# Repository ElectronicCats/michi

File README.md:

# Michi

</p>

  Michi is an electronic board designed by Electronic Cats that simulates configurable keyboard and mouse keys. It has the feature of being able to connect to any conductive material, turning these objects into touch panels. 

  It is an experiment kit for beginners and experts looking to interact between the real world and technology. The Michi can cover the areas of plastic arts, visual arts, music, sports, engineering and even physical rehabilitation.

## For whom is Michi? 

  People 6 years and older, educators, artists, engineers, designers, inventors and creators. 

## How does it work?

  The Michi uses high resistance switching to detect when it has made a connection even with materials that are not very conductive (such as leaves, pasta or people). This technique attracts, Michi can also act as a keyboard or mouse. There are 10 inputs on the front of the board, which can be linked via alligator wires or any other method you can think of. There are another 5 inputs on the back, 3 for keyboard keys and 2 for mouse movement, which can be accessed with jumpers.

  For example, when you connect and touch an apple, you make a connection, and Michi sends the computer a keyboard message. The computer sees Michi as an ordinary keyboard (or mouse). Therefore, it works with all programs, operating systems and web pages, since all programs and web pages receive information from the keyboard and mouse.

## What materials work with Michi?

  Any material that can conduct a little electricity will work. Here are some materials that people have used in our workshops: Ketchup or tomato sauce, Pencil Graphite, Finger Paint, Lemons, etc.

  Other materials that work very well: plants, coins, silverware, anything wet, most foods, aluminum foil, water, and hundreds of things we haven't tried.

## What can I do?

  That's up to you! First, load a computer program or any web page. Let's say you load a piano. Then, instead of using the buttons on the computer keyboard to play the piano, you can connect Michi to something fun, like bananas, and the bananas become your piano keys. 

  Or let's say you search for a Pacman game online and draw a joystick with a pencil. Then you can play Pacman by touching the drawing. 
  The kit includes everything you need: Michi Board, alligator cable, USB cable.

## Manual

Visit our Wiki where you can find the manual 📖: [Wiki](https://github.com/ElectronicCats/michi/wiki)

## How to contribute 
 Contributions are welcome! 

Please read the document  [**Contribution Manual**](https://github.com/ElectronicCats/electroniccats-cla/blob/main/electroniccats-contribution-manual.md)  which will show you how to contribute your changes to the project.

✨ Thanks to all our [contributors](https://github.com/ElectronicCats/michi/graphs/contributors)! ✨

See  [**_Electronic Cats CLA_**](https://github.com/ElectronicCats/electroniccats-cla/blob/main/electroniccats-cla.md) for more information.

See the [**community code of conduct**](https://github.com/ElectronicCats/electroniccats-cla/blob/main/electroniccats-community-code-of-conduct.md)   for a vision of the community we want to build and what we expect from it.

### Maintainer

Electronic Cats invests time and resources in providing this open-source design design, please support Electronic Cats and open-source hardware by purchasing products from Electronic Cats!

## Licence

Firmware released under an GNU AGPL v3.0 license. See the [LICENSE](https://www.gnu.org/licenses/agpl-3.0.en.html) file for more information.

Hardware released under an CERN Open Hardware Licence v1.2. See the [LICENSE_HARDWARE](https://ohwr.org/project/licences/wikis/cern-ohl-v1.2) file for more information.

Electronic Cats is a registered trademark, please do not use if you sell these PCBs.

Electronic Cats invests time and resources providing this open source design, please support Electronic Cats and open-source hardware by purchasing products from Electronic Cats!

Designed by Electronic Cats.

30 Jul 2022

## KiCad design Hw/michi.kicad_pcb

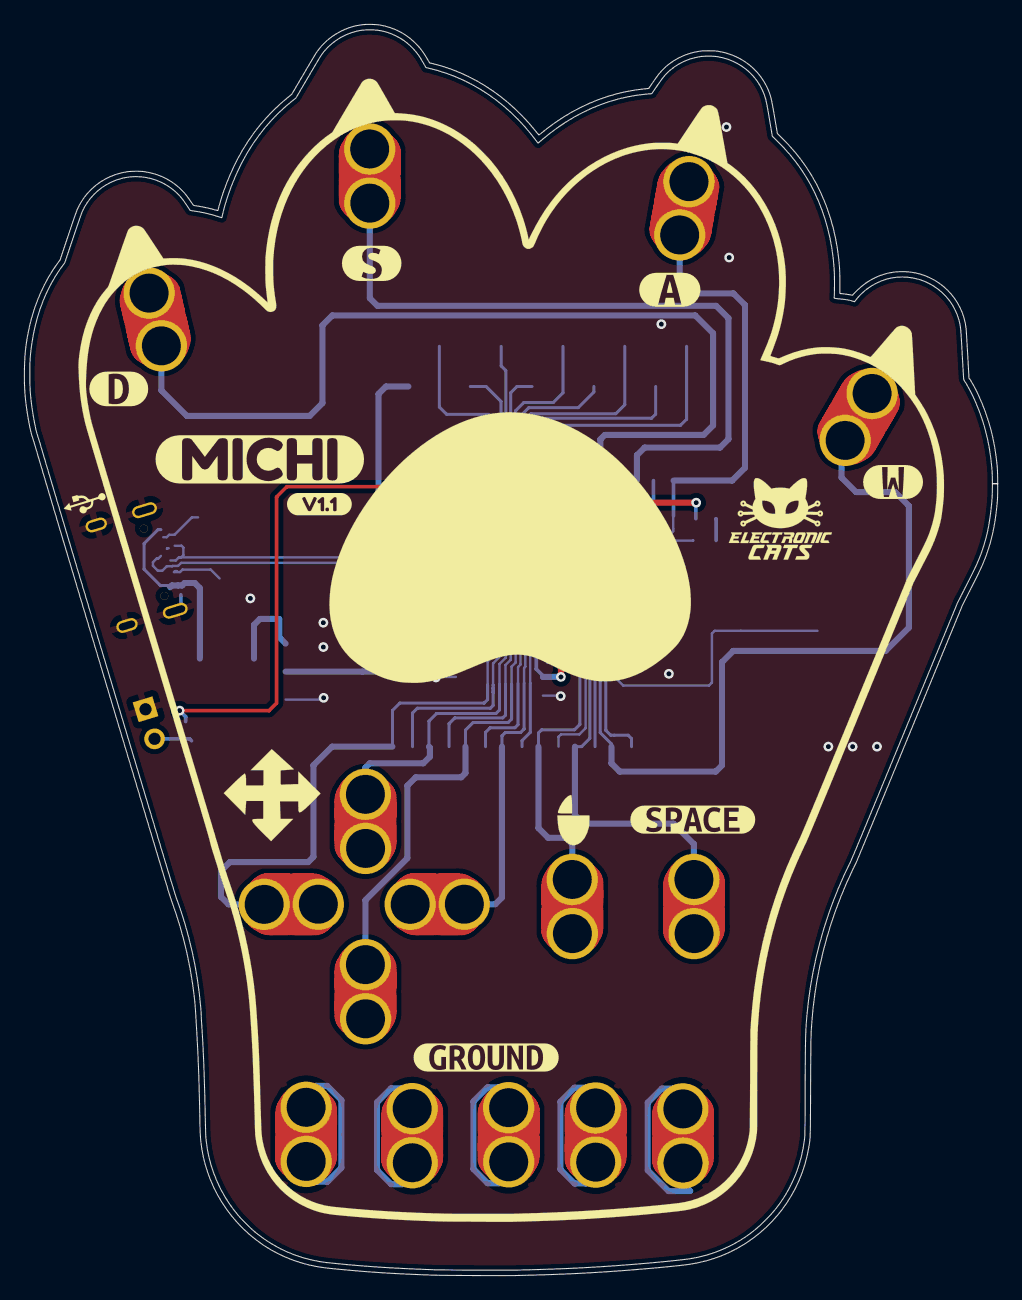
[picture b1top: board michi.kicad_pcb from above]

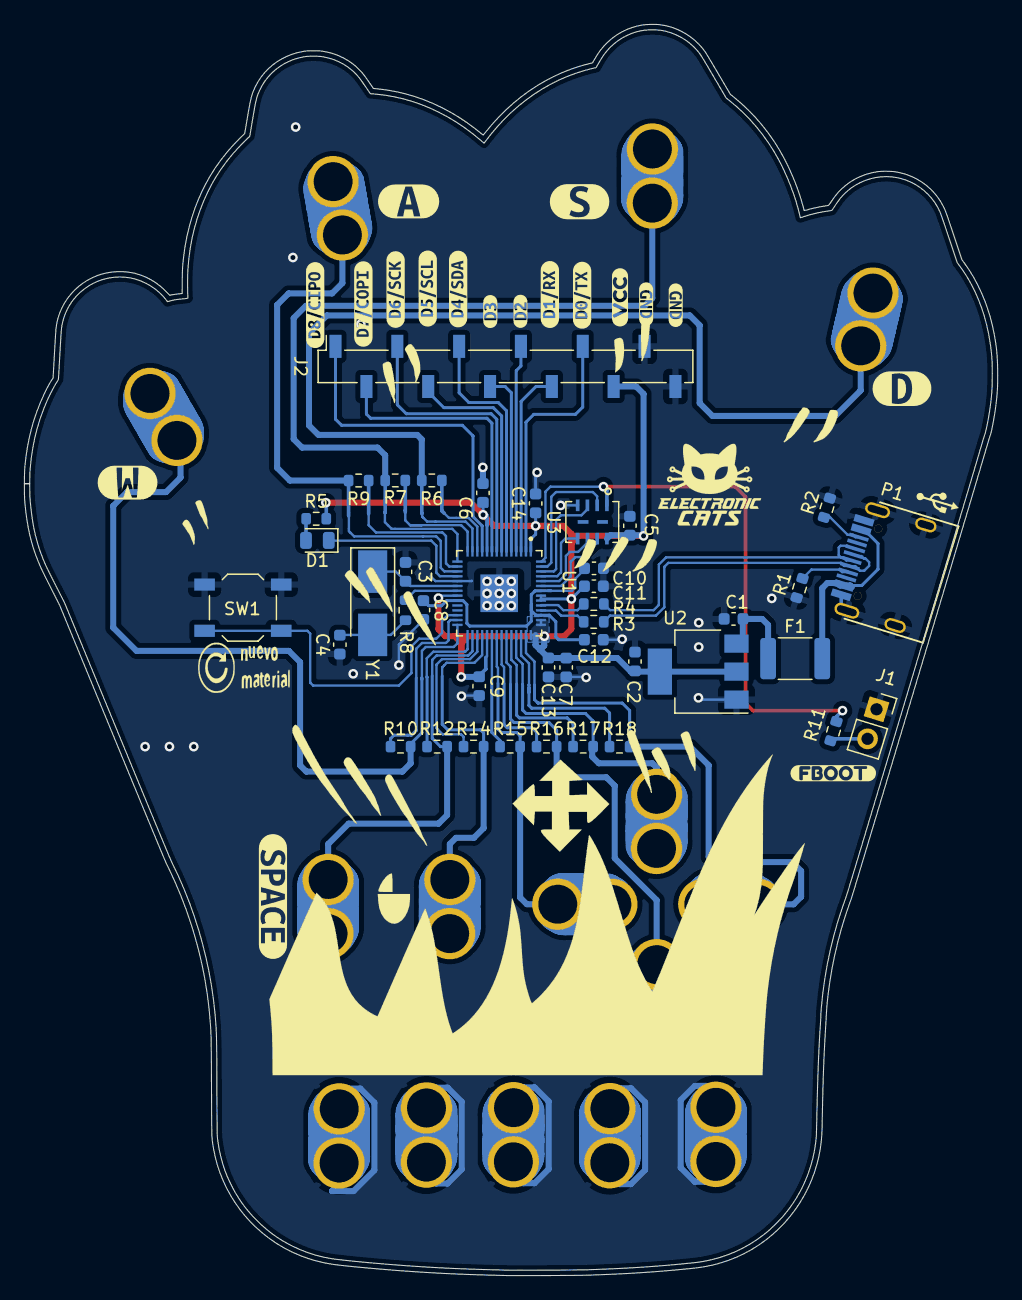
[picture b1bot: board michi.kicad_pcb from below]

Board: 2 copper layers, 80.0 x 102.8 mm, 85 parts (61 on the bottom side), 53 nets.

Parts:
C1, C2: 10uf; C_0603_1608Metric
C3, C4: 27pf; C_0603_1608Metric
C5, C7, C9, C10, C11, C12, C13, C14: .1uf; C_0603_1608Metric
C6, C8: 1uf; C_0603_1608Metric
D1: LED; D_0805_2012Metric
F1: 0.5A; Fuse_1812_4532Metric_Pad1.30x3.40mm_HandSolder
J1: Conn_01x02; PinSocket_1x02_P2.54mm_Vertical
J2: Conn_Right; PinSocket_1x12_P2.54mm_Vertical_SMD_Pin1Right
P1: USB_C_Plug_USB2.0; C393939
P6, P6#2, P6#3, P6#4, P6#5, P6#6, P6#7, P6#8, P6#9, P6#10, P6#11, P6#12, P6#13, P6#14, P6#15: D; SEWALLI_renew
R1, R2: 5.1K; R_0603_1608Metric
R3, R4: 27.4; R_0603_1608Metric
R5, R8, R11: 1k; R_0603_1608Metric
R6, R7, R9, R10, R12, R14, R15, R16, R17, R18: 22M; R_0603_1608Metric
Ref**: Val**; PCB_Michi_Act
SW1: SW_Push; SW_SPST_TL3342
U1: RP2040; QFN40P700X700X90-57N
U2: NCP1117ST33T3G; SOT-223-3_TabPin2
U3: W25Q128JVS; W25Q16JVUUIQ
Y1: Crystal; Crystal_SMD_5032-2Pin_5.0x3.2mm_HandSoldering
kibuzzard-63055E6D, kibuzzard-63055E6D#2: G***; kibuzzard-63055E6D
kibuzzard-63055E8E, kibuzzard-63055E8E#2: G***; kibuzzard-63055E8E
kibuzzard-63055E62, kibuzzard-63055E62#2: G***; kibuzzard-63055E62
kibuzzard-63055EA5, kibuzzard-63055EA5#2: G***; kibuzzard-63055EA5
kibuzzard-63055F28: G***; kibuzzard-63055F28
kibuzzard-63055FE6, kibuzzard-63055FE6#2: G***; kibuzzard-63055FE6
kibuzzard-630561F0: G***; kibuzzard-630561F0
kibuzzard-630562A3, kibuzzard-630562A3#2: G***; kibuzzard-630562A3
kibuzzard-630562BF: G***; kibuzzard-630562BF
kibuzzard-639765AD: G***; kibuzzard-639765AD
kibuzzard-639765C9: G***; kibuzzard-639765C9
kibuzzard-6305622D: G***; kibuzzard-6305622D
kibuzzard-6305624B: G***; kibuzzard-6305624B
kibuzzard-6305640E: G***; kibuzzard-6305640E
kibuzzard-6449595B: G***; kibuzzard-6449595B
kibuzzard-63056210: G***; kibuzzard-63056210
kibuzzard-63056260: G***; kibuzzard-63056260
kibuzzard-63056270: G***; kibuzzard-63056270
kibuzzard-63056280: G***; kibuzzard-63056280
kibuzzard-63056299: G***; kibuzzard-63056299
svg2mod, svg2mod#2: G***; usb_graphic

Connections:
+1V1: C8.1, C10.1, C12.1, U1.23 (DVDD), U1.45 (VREG_VOUT), U1.50 (DVDD)
+3V3: C2.1, C5.1, C6.1, C7.1, C9.1, C11.1, C13.1, C14.1, J2.10, R5.2, U1.1 (IOVDD), U1.10 (IOVDD), U1.22 (IOVDD), U1.33 (IOVDD), U1.42 (IOVDD), U1.43 (ADC_AVDD), U1.44 (VREG_VIN), U1.48 (USB_VDD), U1.49 (IOVDD), U2.2 (VO), U3.8 (VCC)
/D+: P1.A6 (D+), R4.2
/D-: P1.A7 (D-), R3.2
/DR+: R4.1, U1.47 (USB_DP)
/DR-: R3.1, U1.46 (USB_DM)
/IO0: J2.9, U1.2 (GPIO0)
/IO1: J2.8, U1.3 (GPIO1)
/IO2: J2.7, U1.4 (GPIO2)
/IO3: J2.6, U1.5 (GPIO3)
/IO4: J2.5, U1.6 (GPIO4)
/IO5: J2.4, U1.7 (GPIO5)
/IO6: J2.3, U1.8 (GPIO6)
/IO7: J2.2, U1.9 (GPIO7)
/IO8: J2.1, U1.11 (GPIO8)
/IO9: R6.2, U1.12 (GPIO9)
/IO10: P6#10.1, R6.1, U1.13 (GPIO10)
/IO11: R7.2, U1.14 (GPIO11)
/IO12: P6#12.1, R7.1, U1.15 (GPIO12)
/IO13: R9.2, U1.16 (GPIO13)
/IO14: P6.1, R9.1, U1.17 (GPIO14)
/IO15: D1.1 (K), U1.18 (GPIO15)
/IO16: R10.2, U1.27 (GPIO16)
/IO17: P6#11.1, R10.1, U1.28 (GPIO17)
/IO18: R12.2, U1.29 (GPIO18)
/IO19: P6#15.1, R12.1, U1.30 (GPIO19)
/IO20: R14.2, U1.31 (GPIO20)
/IO21: P6#8.1, R14.1, U1.32 (GPIO21)
/IO22: R15.2, U1.34 (GPIO22)
/IO23: P6#6.1, R15.1, U1.35 (GPIO23)
/IO24: R16.2, U1.36 (GPIO24)
/IO25: P6#2.1, R16.1, U1.37 (GPIO25)
/IO26: R17.2, U1.38 (GPIO26/ADC0)
/IO27: P6#3.1, R17.1, U1.39 (GPIO27/ADC1)
/IO28: R18.2, U1.40 (GPIO28/ADC2)
/IO29: P6#7.1, R18.1, U1.41 (GPIO29/ADC3)
/RST: SW1.1, U1.26 (RUN)
/SCLK: U1.52 (QSPI_SCLK), U3.6 (CLK)
/SD1: U1.55 (QSPI_SD1), U3.2 (DO(IO1))
/SD2: U1.54 (QSPI_SD2), U3.3 (IO2)
/SD3: U1.51 (QSPI_SD3), U3.7 (IO3)
/SDO: U1.53 (QSPI_SD0), U3.5 (DI(IO0))
/SS: R11.2, U1.56 (QSPI_CSN), U3.1 (~CS)
/XIN: C3.2, U1.20 (XIN), Y1.1
/XOUT: R8.1, U1.21 (XOUT)
GND: C1.2, C2.2, C3.1, C4.1, C5.2, C6.2, C7.2, C8.2, C9.2, C10.2, C11.2, C12.2, C13.2, C14.2, J1.1, J2.11, J2.12, P1.A1 (GND), P1.S1 (SHIELD), P6#4.1, P6#5.1, P6#9.1, P6#13.1, P6#14.1, R1.2, R2.2, SW1.2, U1.19 (TESTEN), U1.57 (GND), U2.1 (GND), U3.4 (GND)
unnamed: C4.2, R8.2, Y1.2
unnamed: D1.2 (A), R5.1
unnamed: F1.2, P1.A4 (VBUS)
unnamed: J1.2, R11.1
unnamed: P1.A5 (CC), R1.1
unnamed: P1.B5 (VCONN), R2.1
VBUS: C1.1, F1.1, U2.3 (VI)

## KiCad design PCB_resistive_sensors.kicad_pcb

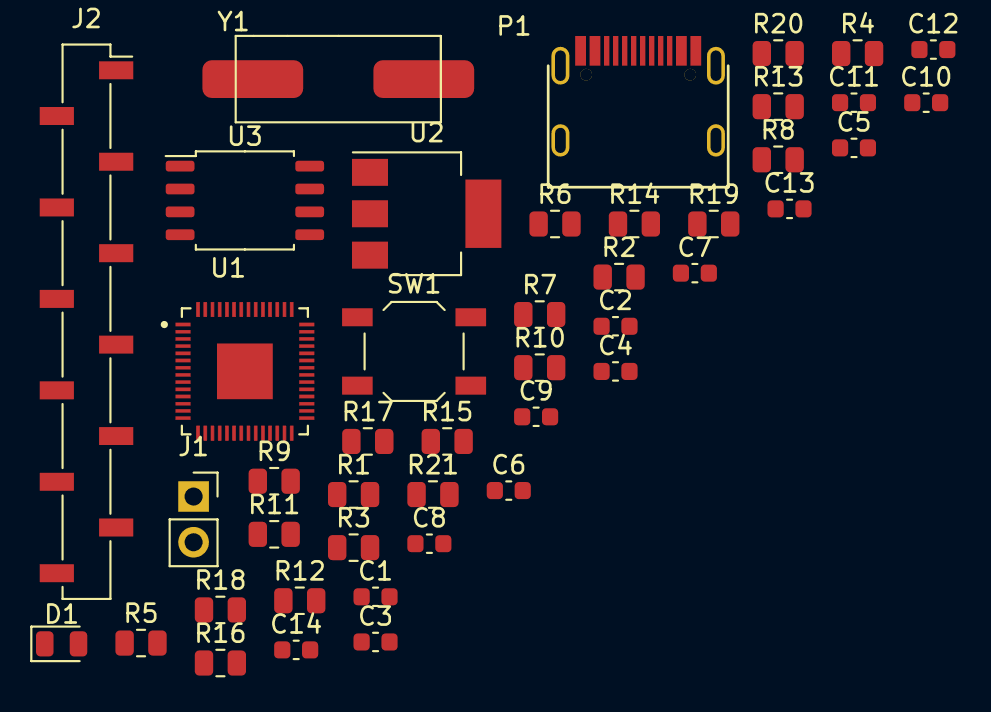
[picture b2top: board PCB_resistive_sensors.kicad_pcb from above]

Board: 2 copper layers, 44 parts (0 on the bottom side), 51 nets, no tracks yet.

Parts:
C1, C2: 10uf; C_0603_1608Metric
C3, C4: 27pf; C_0603_1608Metric
C5, C7, C9, C10, C11, C12, C13, C14: .1uf; C_0603_1608Metric
C6, C8: 1uf; C_0603_1608Metric
D1: LED; D_0805_2012Metric
J1: Conn_01x02; PinSocket_1x02_P2.54mm_Vertical
J2: Conn_Right; PinSocket_1x12_P2.54mm_Vertical_SMD_Pin1Right
P1: USB_C_Plug_USB2.0; C393939
R1, R2: 5.1K; R_0805_2012Metric
R3, R4: 27.4; R_0805_2012Metric
R5, R8, R11: 1k; R_0805_2012Metric
R6, R7, R9, R10, R12, R14, R15, R16, R17, R18, R19, R20: 22M; R_0805_2012Metric
R13: DNF; R_0805_2012Metric
R21: 10k; R_0805_2012Metric
SW1: SW_Push; SW_SPST_TL3342
U1: RP2040; QFN40P700X700X90-57N
U2: NCP1117ST33T3G; SOT-223-3_TabPin2
U3: W25Q128JVS; SOIC-8_5.23x5.23mm_P1.27mm
Y1: Crystal; ABLS-12.000MHZ-B4-T

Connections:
+1V1: C8.1, C10.1, C12.1, U1.23 (DVDD), U1.45 (VREG_VOUT), U1.50 (DVDD)
+3V3: C2.1, C5.1, C6.1, C7.1, C9.1, C11.1, C13.1, C14.1, R5.2, R13.2, R21.2, U1.1 (IOVDD), U1.10 (IOVDD), U1.22 (IOVDD), U1.33 (IOVDD), U1.42 (IOVDD), U1.43 (ADC_AVDD), U1.44 (VREG_VIN), U1.48 (USB_VDD), U1.49 (IOVDD), U2.2 (VO), U3.8 (VCC)
/D+: P1.A6 (D+), R4.2
/D-: P1.A7 (D-), R3.2
/IO0: R6.2, U1.2 (GPIO0)
/IO1: R6.1, U1.3 (GPIO1)
/IO2: R9.2, U1.4 (GPIO2)
/IO3: R9.1, U1.5 (GPIO3)
/IO4: R12.2, U1.6 (GPIO4)
/IO5: R12.1, U1.7 (GPIO5)
/IO6: R15.2, U1.8 (GPIO6)
/IO7: R15.1, U1.9 (GPIO7)
/IO8: R17.2, U1.11 (GPIO8)
/IO9: R17.1, U1.12 (GPIO9)
/IO10: R19.2, U1.13 (GPIO10)
/IO11: R19.1, U1.14 (GPIO11)
/IO12: R7.2, U1.15 (GPIO12)
/IO13: R7.1, U1.16 (GPIO13)
/IO14: R10.2, U1.17 (GPIO14)
/IO15: R10.1, U1.18 (GPIO15)
/IO16: R14.2, U1.27 (GPIO16)
/IO17: R14.1, U1.28 (GPIO17)
/IO18: R16.2, U1.29 (GPIO18)
/IO19: R16.1, U1.30 (GPIO19)
/IO21: R18.2, U1.32 (GPIO21)
/IO22: R18.1, U1.34 (GPIO22)
/IO23: R20.2, U1.35 (GPIO23)
/IO24: R20.1, U1.36 (GPIO24)
/IO25: J2.1, U1.37 (GPIO25)
/IO26: J2.2, U1.38 (GPIO26/ADC0)
/IO27: J2.3, U1.39 (GPIO27/ADC1)
/IO28: J2.4, U1.40 (GPIO28/ADC2)
/IO29: J2.5, U1.41 (GPIO29/ADC3)
/RST: R21.1, SW1.1, U1.26 (RUN)
/SCLK: U1.52 (QSPI_SCLK), U3.6 (CLK)
/SD1: U1.55 (QSPI_SD1), U3.2 (DO(IO1))
/SD2: U1.54 (QSPI_SD2), U3.3 (IO2)
/SD3: U1.51 (QSPI_SD3), U3.7 (IO3)
/SDO: U1.53 (QSPI_SD0), U3.5 (DI(IO0))
/SS: R11.2, R13.1, U1.56 (QSPI_CSN), U3.1 (~CS)
/XIN: C3.2, U1.20 (XIN), Y1.1
/XOUT: R8.2, U1.21 (XOUT)
GND: C1.2, C2.2, C3.1, C4.1, C5.2, C6.2, C7.2, C8.2, C9.2, C10.2, C11.2, C12.2, C13.2, C14.2, D1.1 (K), J1.1, P1.A1 (GND), P1.S1 (SHIELD), R1.2, R2.2, SW1.2, U1.19 (TESTEN), U1.57 (GND), U2.1 (GND), U3.4 (GND)
unnamed: C4.2, R8.1, Y1.2
unnamed: D1.2 (A), R5.1
unnamed: J1.2, R11.1
unnamed: P1.A5 (CC), R1.1
unnamed: P1.B5 (VCONN), R2.1
unnamed: R3.1, U1.46 (USB_DM)
unnamed: R4.1, U1.47 (USB_DP)
VBUS: C1.1, P1.A4 (VBUS), U2.3 (VI)

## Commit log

2022-06-30 Added project
2022-06-30 Created "Hw" carpet
2022-06-30 add gitignore
2022-06-30 anotate changes
2022-08-15 rename files hardware
2022-08-15 Added Art Michi
2022-08-19 Floorplan placement
2022-08-22 Started PCB routing
2022-08-22 Fixed PCB outline
2022-08-22 Resisitive sensors connected
2022-08-23 Edge.Cuts generated
2022-08-23 Reverse footprint
2022-08-23 Add labels
2022-08-24 fix footprints
2022-08-24 Resize
2022-08-24 update v1.0 layout
2022-08-30 Update BOM
2022-09-06 Init firmware
2022-09-06 Update labels schematic
2022-09-06 add file uf2
2022-10-21 Fixed mouse bug
2022-12-12 fix label VCC 3v3
2023-04-26 label v1.1
2023-10-27 change R3 & R4 #manf for stock
2024-04-09 feta (docs): Update README.md
    Hww to contribute added
